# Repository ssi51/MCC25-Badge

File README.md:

# MCC25 Badge

## 🦇 Introduction

Welcome to the official repository for the **MCC 25' Badge**, a custom electronic conference badge based on the open-source [Hackbat Badge](https://hackaday.io/project/197688-hackbat-badge).

**📡 Repository Updates & Future Code**
This repository is the central hub for the MCC 25' Badge ecosystem. **It will be regularly updated with new firmware, games, and example codes.** We encourage you to "Watch" or "Star" this repository to get notified when new features are available to upload to your badge.

## ✨ Features

* **Wireless Connectivity**: Integrated 2.4GHz WiFi and Bluetooth 5.0 (LE) via the ESP32-C3.
* **Crisp Display**: 1.3-inch OLED screen for menus, games, and status updates.
* **Interactive Controls**: 6-button interface (D-Pad + A/B buttons) designed for gaming and navigation.
* **RGB Lighting**: 4x Addressable WS2812 LEDs for visual notifications and light shows.
* **Portable Power**: Runs on USB-C or AA batteries with dedicated power management.
* **Open Development**: Compatible with Arduino IDE and Espressif ESP-IDF.

## 🛠 Hardware Specifications

| Component | Specification |
| :--- | :--- |
| **Microcontroller** | Espressif **ESP32-C3** (RISC-V Single-core @ 160MHz) |
| **Display** | 1.3" OLED (SH110x / SSD1306 compatible) |
| **Connectivity** | WiFi 802.11b/g/n + Bluetooth LE 5.0 |
| **User Input** | 6 Push Buttons (Up, Down, Left, Right, A, B) |
| **LEDs** | 4 x WS2812B Addressable RGB LEDs |
| **Dimensions** | 100mm x 60mm |
| **Power Input** | USB Micro or 3x AA Battery Holder (Back mounted) |

## 🚀 Getting Started

### Prerequisites

To program the MCC25 Badge, you will need to install the necessary drivers and boards.

1.  **Install Arduino IDE**: Download from the [official website](https://www.arduino.cc/en/software).
2.  **Add ESP32 Board Manager**:
    * Go to `File` > `Preferences`.
    * Add the following URL to "Additional Board Manager URLs":
        `https://raw.githubusercontent.com/espressif/arduino-esp32/gh-pages/package_esp32_index.json`
    * Go to `Tools` > `Board` > `Boards Manager`, search for "ESP32", and install.

### Flashing Your First Sketch

1.  Select the board: `ESP32C3 Dev Module`.
2.  Ensure `USB CDC On Boot` is set to "Enable" if you are using the USB port for serial debugging.
3.  Connect your MCC25 Badge via USB-Micro.
4.  Select the correct Port under `Tools` > `Port`.
5.  Upload the example `Blink` or `DisplayTest` sketch from the `/examples` folder in this repo.

## 🔋 Powering the Badge

The MCC25 Badge can be powered in two ways:
1.  **USB Mode**: Connect a USB Micro cable for power and programming.
2.  **Battery Mode**: Insert 3x AA batteries into the rear holder. Use the physical slide switch to toggle battery power ON/OFF.
    * *Note: Ensure batteries are removed if you are modifying hardware components.*

## 📂 Repository Structure

* `/examples` - Source code, future updates, and example sketches.
* `/hardware` - PCB design files (Gerbers, Schematics).
* `/docs` - Datasheets and additional documentation.

## 🤝 Credits & Acknowledgments

* **Original Design**: Based on the **Hackbat Badge** by [Pablo on Hackaday.io](https://hackaday.io/project/197688-hackbat-badge).
* **MCU**: Powered by Espressif Systems.

## 📄 License

This project is open-source.

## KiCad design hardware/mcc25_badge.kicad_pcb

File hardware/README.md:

# 🛠️ MCC25 Badge Hardware Design

This directory contains the Open Source Hardware (OSHW) design files for the **MCC25 Badge**. The PCB was designed using **KiCad** (Version 7.0+).

## 📂 File Descriptions

| File Name | Description |
| :--- | :--- |
| `mcc25_badge.kicad_pro` | Main KiCad Project file. Open this to start editing. |
| `mcc25_badge.kicad_sch` | **Schematic**: Shows how the ESP32-C3 connects to the OLED, LEDs, and buttons. |
| `mcc25_badge.kicad_pcb` | **PCB Layout**: The physical board routing, layers, and footprints. |
| `gerber.zip` | **Production Files**: The exact manufacturing files needed to order this board from a fab house. |

## 📐 Technical Specifications
* **Layers:** 2-Layer PCB
* **Dimensions:** 100mm x 60mm
* **Thickness:** 1.6mm (Standard)
* **Signal Voltage:** 3.3V Logic

## 🏭 How to Order This Board (Fabrication)

You don't need to install KiCad if you just want to manufacture the PCB.

1.  **Download the Gerbers**: Download the file `gerber.zip` from this folder.
2.  **Visit a Manufacturer**: Go to a PCB fabrication website (e.g., JLCPCB, PCBWay, AiPCBA).
3.  **Upload**: Drag and drop the `gerber.zip` file into their "Quote" tool.
4.  **Select Settings**: The defaults are usually fine, but ensure the following:
    * **Layers**: 2
    * **Thickness**: 1.6mm
    * **PCB Color**: Black (Matches the MCC aesthetic)
    * **Surface Finish**: HASL (Cheaper) or ENIG (Better for gold pads)
5.  **Order**: Add to cart and ship!

## ✏️ How to Modify the Design

If you want to change the logo, move buttons, or add sensors:

1.  Install **KiCad** (Free & Open Source) from [kicad.org](https://www.kicad.org/).
2.  Clone this repository to your computer.
3.  Double-click `mcc25_badge.kicad_pro` to open the project manager.
4.  Open the **Schematic Editor** to change connections or the **PCB Editor** to change the physical layout.

## ⚠️ Assembly Note
This board uses **SMD (Surface Mount Device)** components for the ESP32-C3 and LEDs.
* If ordering **PCB Assembly (PCBA)** services, you will need to provide them with the `BOM` (Bill of Materials) and `CPL` (Component Placement List).
* If assembling by hand, ensure you have a hot air station or a fine-tip soldering iron.

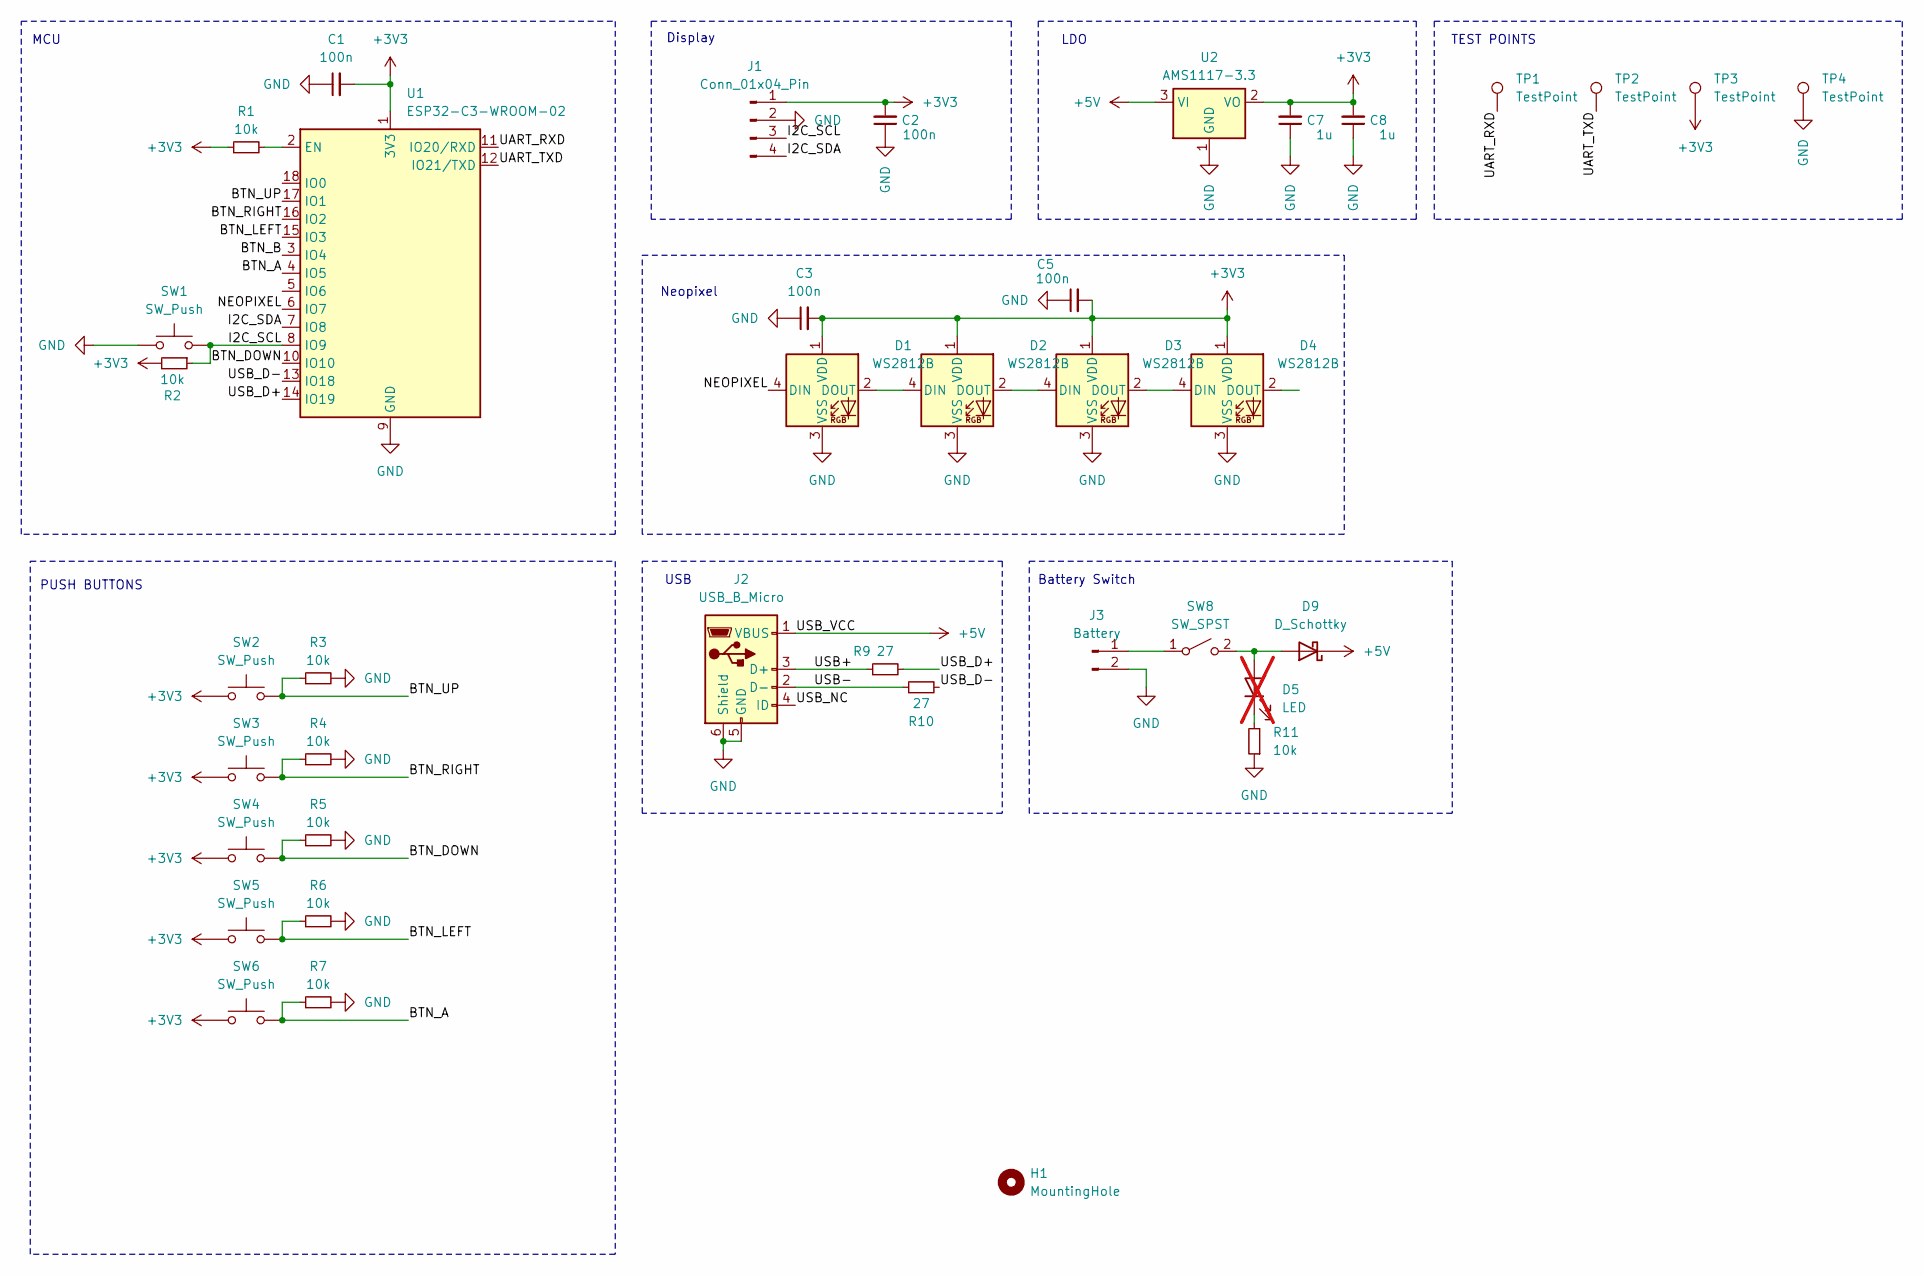
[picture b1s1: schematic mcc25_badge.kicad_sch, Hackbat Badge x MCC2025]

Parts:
C1, C2, C3, C5: 100n; C_0402_1005Metric
C7, C8: 1u; C_0805_2012Metric
D1, D2, D3, D4: WS2812B; LED_WS2812B_PLCC4_5.0x5.0mm_P3.2mm; JLCPCB Part # C2920042
D5: LED; LED_0805_2012Metric; not fitted
D9: D_Schottky; Nexperia_CFP3_SOD-123W; JLCPCB Part # C82544
H1: MountingHole; MountingHole_3.2mm_M3
J1: Conn_01x04_Pin; PinSocket_1x04_P2.54mm_Vertical
J2: USB_B_Micro; USB_Micro-B_Amphenol_10118193-0001LF_Horizontal; JLCPCB Part # C132562
J3: Battery; PinSocket_1x02_P2.54mm_Vertical_SMD_Pin1Left
R1, R2, R3, R4, R5, R6, R7, R11: 10k; R_0402_1005Metric
R9, R10: 27; R_0402_1005Metric
SW1: SW_Push; SW_Push_SPST_NO_Alps_SKRK; JLCPCB Part # C115357
SW2, SW3, SW4, SW5, SW6: SW_Push; SW_Push_1P1T_NO_6x6mm_H9.5mm; JLCPCB Part # C455109
SW8: SW_SPST; SW_SPDT_CK_JS102011SAQN; JLCPCB Part # C92658
TP1, TP2, TP3, TP4: TestPoint; TestPoint_Pad_D1.0mm
U1: ESP32-C3-WROOM-02; JLCPCB Part # C2934560
U2: AMS1117-3.3; SOT-223-3_TabPin2

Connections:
+3V3: C1.2, C2.2, C3.2, C5.2, C7.2, C8.2, D1.1 (VDD), D2.1 (VDD), D3.1 (VDD), D4.1 (VDD), J1.1, R1.1, R2.2, SW2.1, SW3.1, SW4.1, SW5.1, SW6.1, TP3.1, U1.1 (3V3), U2.2 (VO)
+5V: D9.1 (K), J2.1 (VBUS), U2.3 (VI)
/BTN_A: R7.1, SW6.2, U1.4 (IO5)
/BTN_B: U1.3 (IO4)
/BTN_DOWN: R5.1, SW4.2, U1.10 (IO10)
/BTN_LEFT: R6.1, SW5.2, U1.15 (IO3)
/BTN_RIGHT: R4.1, SW3.2, U1.16 (IO2)
/BTN_UP: R3.1, SW2.2, U1.17 (IO1)
/I2C_SCL: J1.3, R2.1, SW1.2, U1.8 (IO9)
/I2C_SDA: J1.4, U1.7 (IO8)
/NEOPIXEL: D1.4 (DIN), U1.6 (IO7)
/UART_RXD: TP1.1, U1.11 (IO20/RXD)
/UART_TXD: TP2.1, U1.12 (IO21/TXD)
/USB+: J2.3 (D+), R9.1
/USB-: J2.2 (D-), R10.1
/USB_D+: R9.2, U1.14 (IO19)
/USB_D-: R10.2, U1.13 (IO18)
/USB_NC: J2.4 (ID)
GND: C1.1, C2.1, C3.1, C5.1, C7.1, C8.1, D1.3 (VSS), D2.3 (VSS), D3.3 (VSS), D4.3 (VSS), J1.2, J2.5 (GND), J2.6 (Shield), J3.2, R3.2, R4.2, R5.2, R6.2, R7.2, R11.1, SW1.1, TP4.1, U1.9 (GND), U1.19 (GND), U2.1 (GND)
unnamed: D1.2 (DOUT), D2.4 (DIN)
unnamed: D2.2 (DOUT), D3.4 (DIN)
unnamed: D3.2 (DOUT), D4.4 (DIN)
unnamed: D5.2 (A), D9.2 (A), SW8.2 (B)
unnamed: D5.1 (K), R11.2
unnamed: J3.1, SW8.1 (A)
unnamed: R1.2, U1.2 (EN)

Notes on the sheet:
LDO
Display
USB
MCU
Neopixel
TEST POINTS
PUSH BUTTONS
Battery Switch

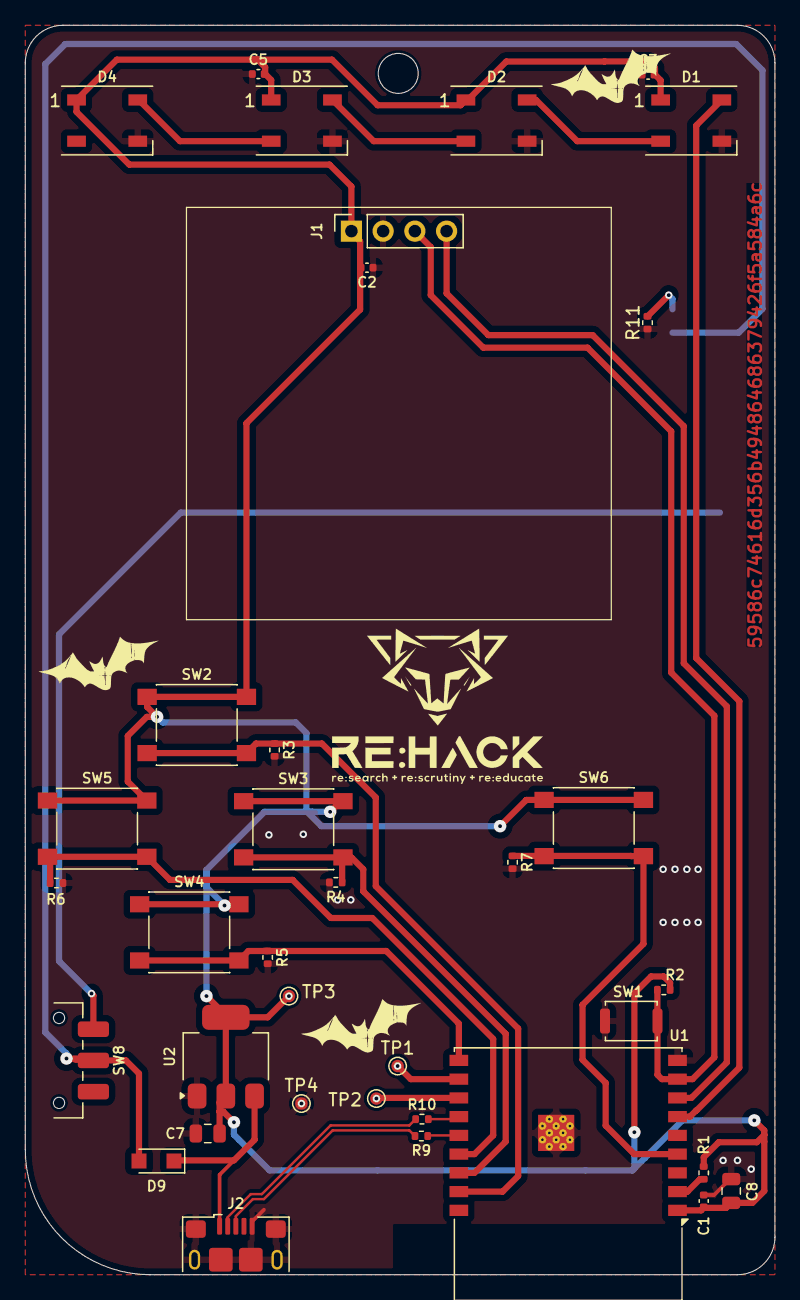
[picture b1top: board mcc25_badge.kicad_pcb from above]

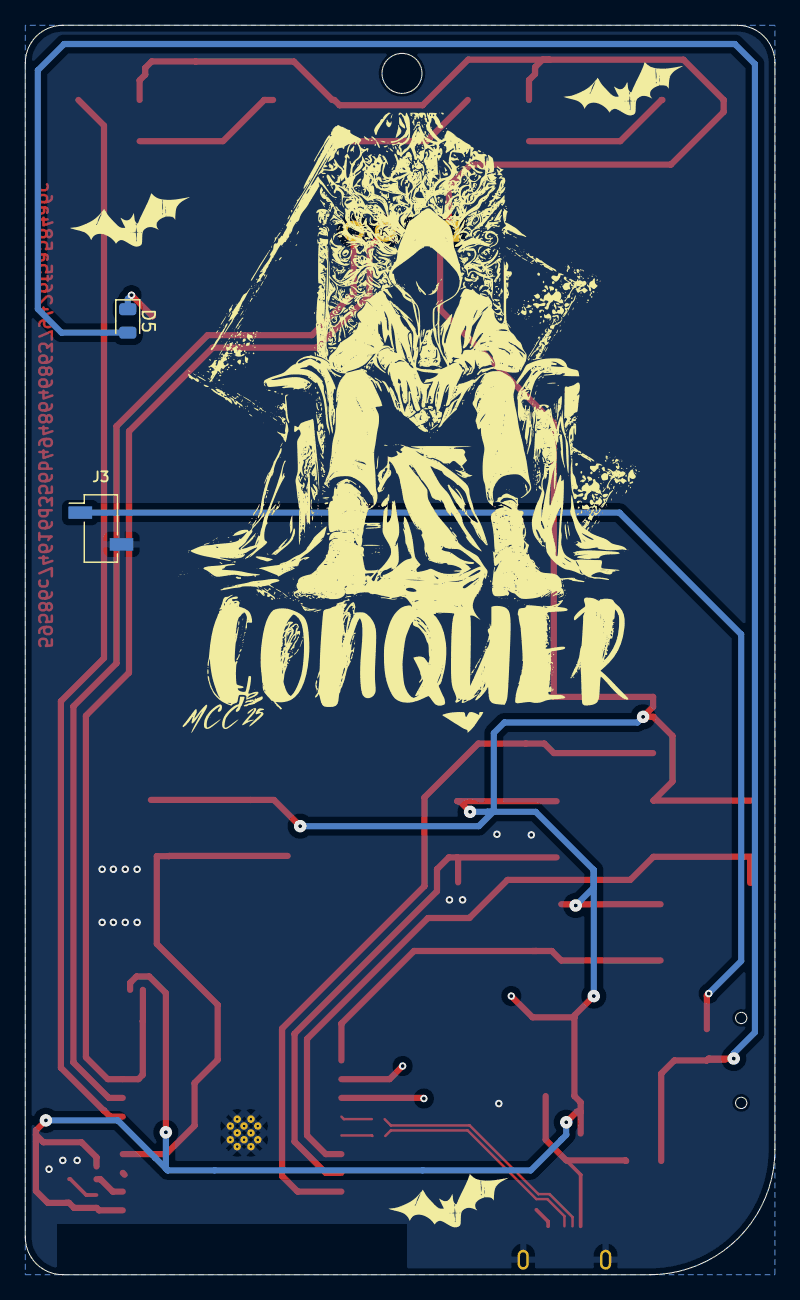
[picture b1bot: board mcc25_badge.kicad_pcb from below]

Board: 2 copper layers, 60.0 x 100.0 mm, 39 parts (2 on the bottom side), 24 nets.

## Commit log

2025-11-28 Revise README with project introduction and features
    Updated README.md to enhance project details and features.
2025-11-28 Create README for MCC25 Badge firmware
    Add initial README for Village Night firmware with features and library requirements.
2025-11-28 Add README for Party Sync Mode firmware
    This README provides an overview of the Party Sync Mode firmware, detailing its features, hardware requirements, library dependencies, and testing instructions.
2025-11-30 Add README for MCC25 Badge hardware design
2025-11-30 Add KiCad hardware design files
2025-11-30 Rename READ.me to README.md
2025-11-30 Change USB connection type for MCC25 Badge
    Updated connection instructions for MCC25 Badge.

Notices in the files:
README.md:
License: MIT
